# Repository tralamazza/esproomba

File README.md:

# esproomba

Roomba WiFi adapter.

## License

Hardware licensed under the **CERN OHL 1.2** (see ```hardware/LICENSE```).

Software/firmware licensed under GPLv3.

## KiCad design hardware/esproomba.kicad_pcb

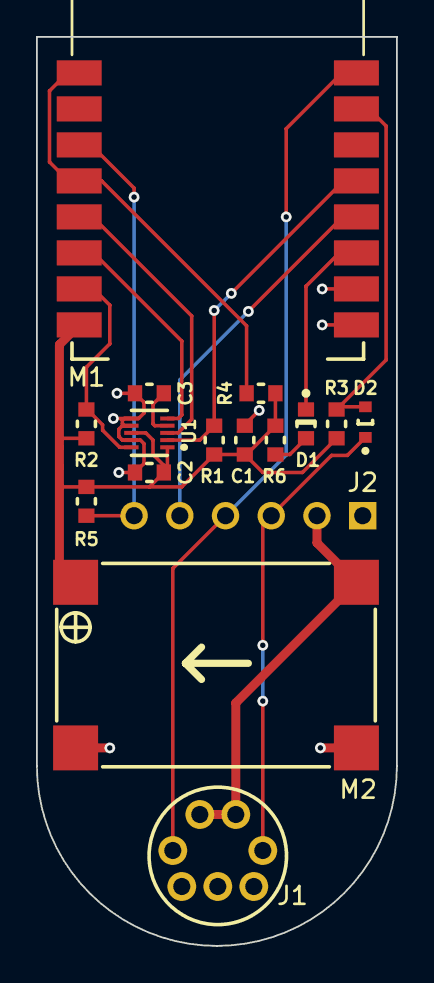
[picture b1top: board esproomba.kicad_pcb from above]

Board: 2 copper layers, 20.0 x 50.5 mm, 16 parts (0 on the bottom side), 16 nets.

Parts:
C1: 1uF; SMD-1608
C2, C3: 0.1uF; SMD-1608
D1: LED; SMD-1608-LED
D2: D; SOD-523
J1: CONN-7; MINI-DIN-7
J2: CONN-6
M1: ESP-12
M2: V-REG; MINI-360
R1, R2, R3, R4, R5, R6: 4.7k; SMD-1608
U1: MMA8652FC; DFN-10

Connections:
+3V3: C1.1, C2.1, M1.8, M2.VOUT, R1.1, R2.1, R3.1, R4.1, R5.1, R6.1, U1.1, U1.8
/BATT: J1.1, J1.2, J2.2, M2.VIN
/CH_PD: J2.6, M1.3, R5.2
/GPIO0: J2.5, M1.12
/INT1: M1.6, U1.5
/INT2: M1.5, U1.3
/RX: J1.3, J2.4, M1.16
/SCL: M1.13, R1.2, U1.2
/SDA: M1.7, R2.2, U1.10
/TX: D2.C, J1.4, J2.3
/WAKE: M1.1, M1.4, R4.2
DGND: C1.2, C2.2, C3.2, J1.6, J1.7, J2.1, M1.9, M1.10, M2.GND, U1.6, U1.7, U1.9
unnamed: C3.1, U1.4
unnamed: D1.A, R6.2
unnamed: D1.C, M1.11
unnamed: D2.A, M1.15, R3.2

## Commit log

2015-07-16 v0.1
2015-07-16 license
2015-07-16 kicad libs
2015-08-16 v0.2
